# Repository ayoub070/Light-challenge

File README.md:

# Light-challenge
 This is the kicad file of the light challenge Printed Circuit Board

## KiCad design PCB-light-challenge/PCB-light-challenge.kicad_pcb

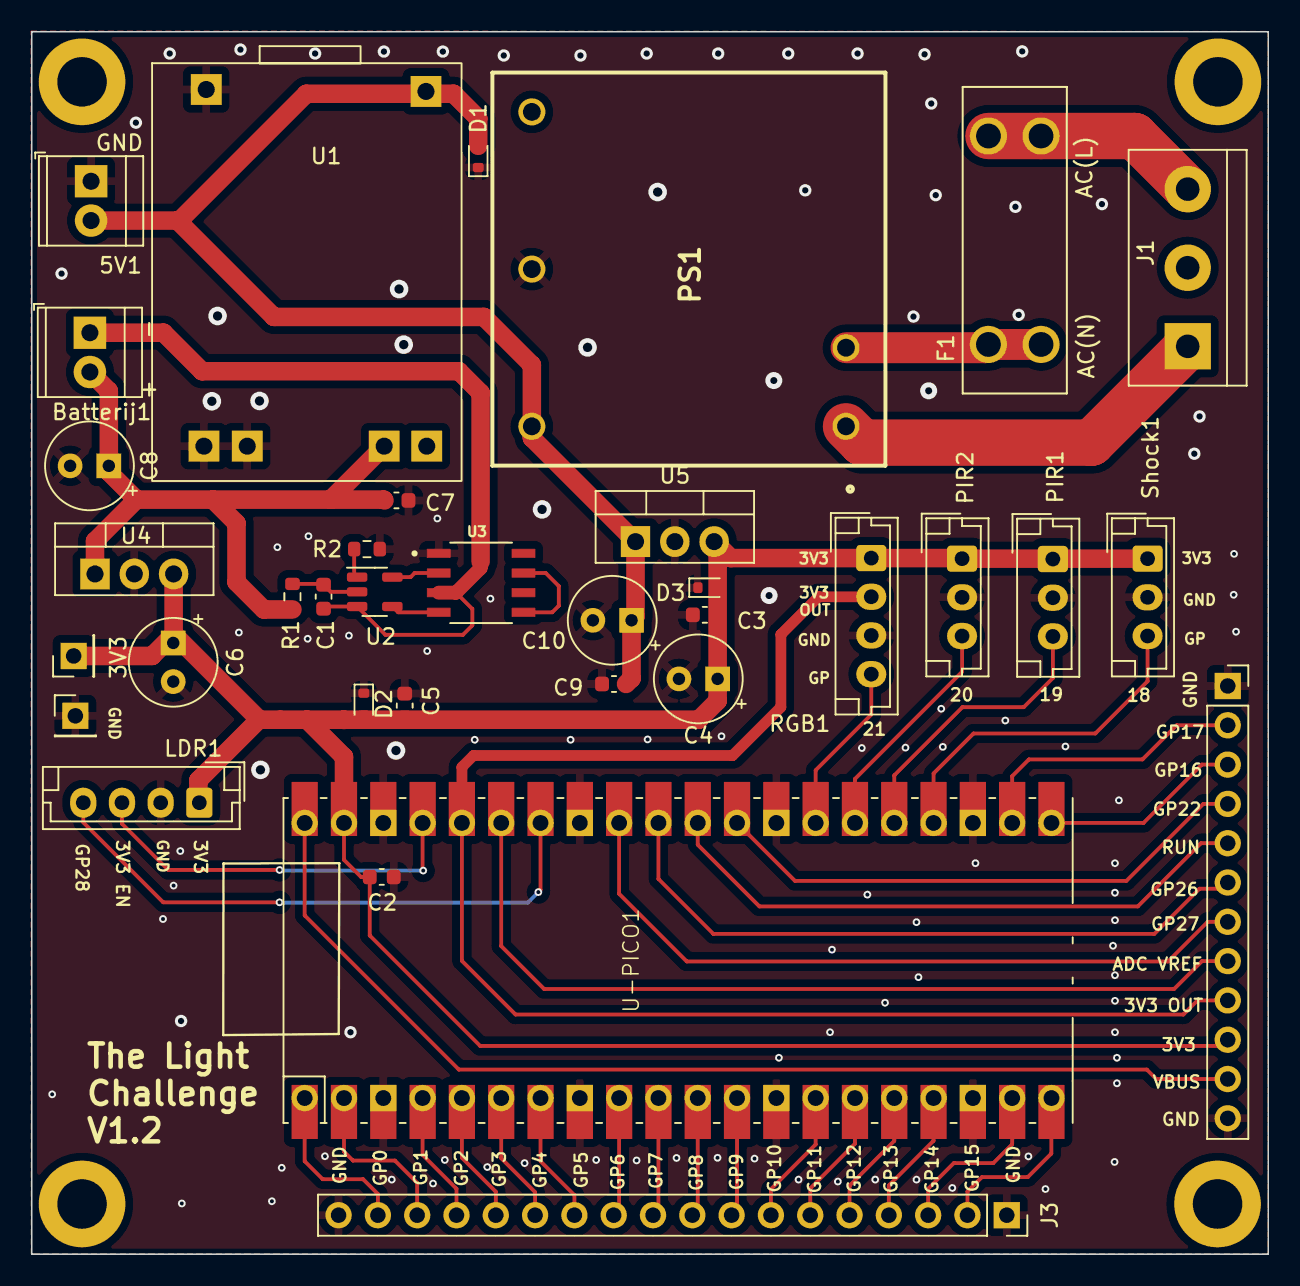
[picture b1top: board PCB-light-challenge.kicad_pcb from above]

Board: 2 copper layers, 79.9 x 79.0 mm, 39 parts (0 on the bottom side), 44 nets.

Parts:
3V3: Conn_01x01_Socket; PinHeader_1x01_P2.54mm_Vertical
5V1: Conn_01x02_Socket; TerminalBlock_TE_282834-2_1x02_P2.54mm_Horizontal
Batterij1: Screw_Terminal_01x02; TerminalBlock_TE_282834-2_1x02_P2.54mm_Horizontal
C1, C2, C3, C5, C7, C9: 100n; C_0603_1608Metric
C4, C6, C8, C10: C_Polarized; CP_Radial_Tantal_D5.5mm_P2.50mm
D1, D2, D3: ESD9B3.3ST5G; D_SOD-523
F1: Fuse; FUSE_3557-2
H1, H2, H3, H4: MountingHole; MountingHole_3.2mm_M3_DIN965_Pad
J1: Screw_Terminal_01x03; TerminalBlock_bornier-3_P5.08mm
J3: Conn_01x18_Socket; PinSocket_1x18_P2.54mm_Vertical
J4: Conn_01x12_Socket; PinSocket_1x12_P2.54mm_Vertical
LDR1: LDR; JST_EH_B4B-EH-A_1x04_P2.50mm_Vertical
P-1: Conn_01x01_Socket; PinHeader_1x01_P2.54mm_Vertical
PIR1, PIR2: JST_EH_B3B-EH-A_1x03_P2.50mm_Vertical
PS1: TMPS_05-105; TMPS05-105
R1: 330; R_0603_1608Metric
R2: 2K7; R_0603_1608Metric
RGB1: RGB; JST_EH_B4B-EH-A_1x04_P2.50mm_Vertical
Shock1: JST_EH_B3B-EH-A_1x03_P2.50mm_Vertical
U1: bms
U2: AP9101CK; SOT-23-5
U3: SP8K32FRATB; SOIC127P600X175-8N
U4, U5: TO-220-3_Vertical
U-PICO1: PICO

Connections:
3V3: 3V3.1, C2.1, C3.1, C4.1, C5.1, C6.1, D2.2 (A2), D3.2 (A2), J4.10, LDR1.1, PIR1.1 (VCC), PIR2.1 (VCC), RGB1.1, Shock1.1 (VCC), U4.3 (OUT), U5.3 (OUT), U-PICO1.39 (VSYS)
3V3 EN: LDR1.3, U-PICO1.37 (3V3_EN)
3V3 OUT: J4.9, RGB1.2, U-PICO1.36 (3V3(OUT))
+5V: 5V1.2, C9.1, C10.1, D1.2 (A2), PS1.5 (+VOUT), U1.6 (IN+), U5.1 (IN)
/Battery_charger/Fuse: F1.1_1, F1.1_2, PS1.2 (AC(L))
/Battery_charger/Fuse_in: F1.2_1, F1.2_2, J1.3
/Battery_charger/GNDAC: J1.1, PS1.1 (AC(N))
ADC VREF: J4.8, U-PICO1.35 (ADC_VREF)
Batterij+: Batterij1.2, C7.1, C8.1, R1.1, U1.4 (BAT+), U4.1 (IN)
Batterij-: Batterij1.1, C1.2, U2.3 (VSS), U3.3
GP0: J3.17, U-PICO1.1 (GP0)
GP1: J3.16, U-PICO1.2 (GP1)
GP2: J3.15, U-PICO1.4 (GP2)
GP3: J3.14, U-PICO1.5 (GP3)
GP4: J3.13, U-PICO1.6 (GP4)
GP5: J3.12, U-PICO1.7 (GP5)
GP6: J3.11, U-PICO1.9 (GP6)
GP7: J3.10, U-PICO1.10 (GP7)
GP8: J3.9, U-PICO1.11 (GP8)
GP9: J3.8, U-PICO1.12 (GP9)
GP10: J3.7, U-PICO1.14 (GP10)
GP11: J3.6, U-PICO1.15 (GP11)
GP12: J3.5, U-PICO1.16 (GP12)
GP13: J3.4, U-PICO1.17 (GP13)
GP14: J3.3, U-PICO1.19 (GP14)
GP15: J3.2, U-PICO1.20 (GP15)
GP16: J4.3, U-PICO1.21 (GP16)
GP17: J4.2, U-PICO1.22 (GP17)
GP18: Shock1.3 (Digital_Out), U-PICO1.24 (GP18)
GP19: PIR1.3 (OUT_data), U-PICO1.25 (GP19)
GP20: PIR2.3 (OUT_data), U-PICO1.26 (GP20)
GP21: RGB1.4, U-PICO1.27 (GP21)
GP22: J4.4, U-PICO1.29 (GP22)
GP26: J4.6, U-PICO1.31 (GP26-ADC0)
GP27: J4.7, U-PICO1.32 (GP27-ADC1)
GP28: LDR1.4, U-PICO1.34 (GP28-ADC2)
unnamed: U2.5 (CO), U3.2
unnamed: U2.4 (DO), U3.4
unnamed: C1.1, R1.2, U2.2 (VDD)
unnamed: R2.2, U2.1 (VM)
unnamed: U3.5, U3.7
P-: 5V1.1, C2.2, C3.2, C4.2, C5.2, C6.2, C7.2, C8.2, C9.2, C10.2, D1.1 (A1), D2.1 (A1), D3.1 (A1), J3.1, J3.18, J4.1, J4.12, LDR1.2, P-1.1, PIR1.2 (GND), PIR2.2 (GND), PS1.4 (-VOUT), R2.1, RGB1.3, Shock1.2 (GND), U1.1 (OUT-), U1.3 (BAT-), U1.5 (IN-), U3.1, U4.2 (GND), U5.2 (GND), U-PICO1.3 (GND), U-PICO1.8 (GND), U-PICO1.13 (GND), U-PICO1.18 (GND), U-PICO1.23 (GND), U-PICO1.28 (GND), U-PICO1.33 (GND-AGND), U-PICO1.38 (GND)
RUN: J4.5, U-PICO1.30 (RUN)
VBUS: J4.11, U-PICO1.40 (VBUS)

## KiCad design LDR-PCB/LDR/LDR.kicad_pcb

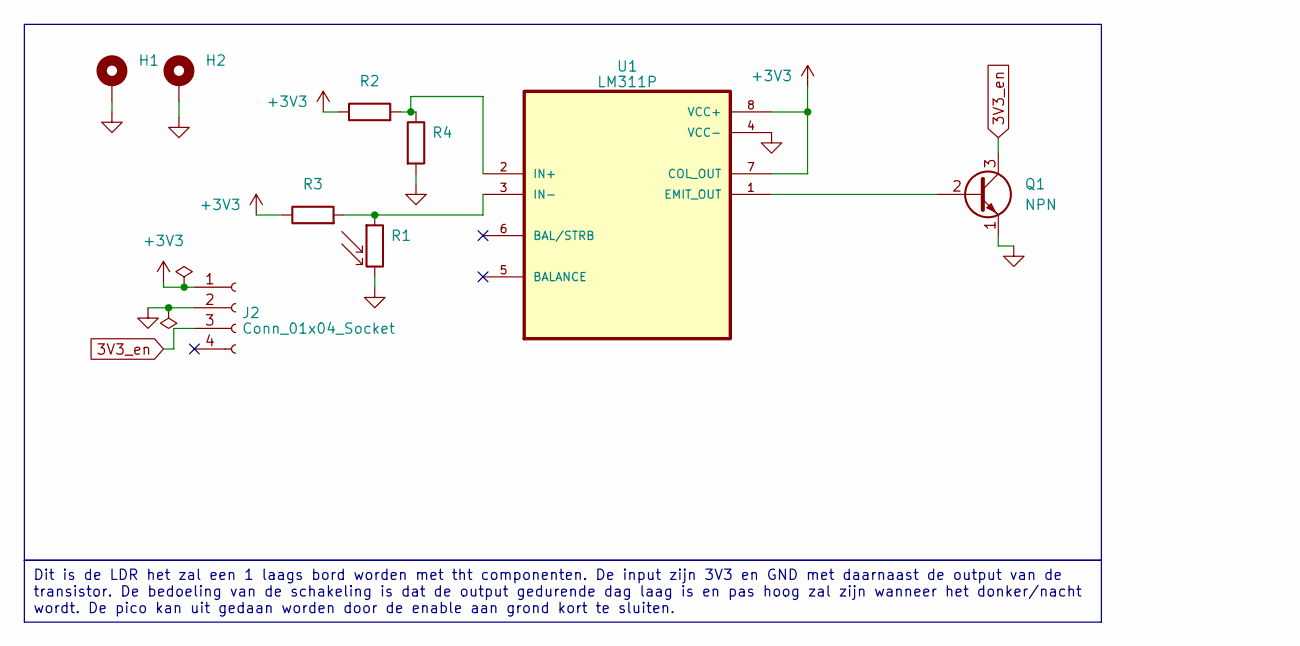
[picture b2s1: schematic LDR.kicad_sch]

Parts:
H1, H2: MountingHole_Pad; MountingHole_2.2mm_M2_ISO14580_Pad
J2: Conn_01x04_Socket; JST_EH_B4B-EH-A_1x04_P2.50mm_Vertical
Q1: NPN; TO-92_Inline
R1: R_Photo; R_Axial_DIN0204_L3.6mm_D1.6mm_P5.08mm_Horizontal
R2, R3: 2K2; R_Axial_DIN0204_L3.6mm_D1.6mm_P5.08mm_Horizontal
R4: 1K8; R_Axial_DIN0204_L3.6mm_D1.6mm_P5.08mm_Horizontal
U1: LM311P; DIP794W45P254L959H508Q8

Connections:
3V3_en: J2.3, Q1.3 (C)
+3V3: J2.1, R2.1, R3.1, U1.7 (COL_OUT), U1.8 (VCC+)
GND: H1.1, H2.1, J2.2, Q1.1 (E), R1.2, R4.2, U1.4 (VCC-)
unnamed: Q1.2 (B), U1.1 (EMIT_OUT)
unnamed: R2.2, R4.1, U1.2 (IN+)
unnamed: R1.1, R3.2, U1.3 (IN-)

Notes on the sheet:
Dit is de LDR het zal een 1 laags bord worden met tht componenten. De input zijn 3V3 en GND met daarnaast de output van de transistor. De bedoeling van de schakeling is dat de output gedurende dag laag is en pas hoog zal zijn wanneer het donker/nacht wordt. De pico kan uit gedaan worden door de ena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

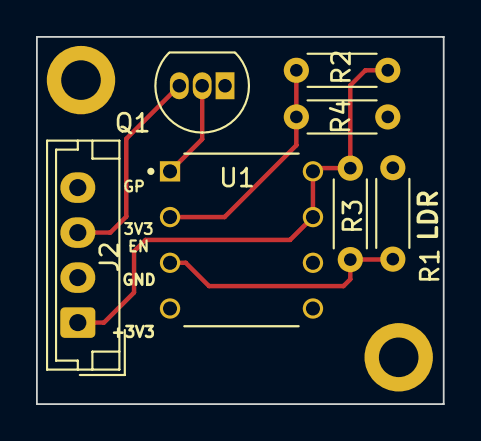
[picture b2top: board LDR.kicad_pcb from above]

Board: 2 copper layers, 22.6 x 20.4 mm, 9 parts (0 on the bottom side), 6 nets.

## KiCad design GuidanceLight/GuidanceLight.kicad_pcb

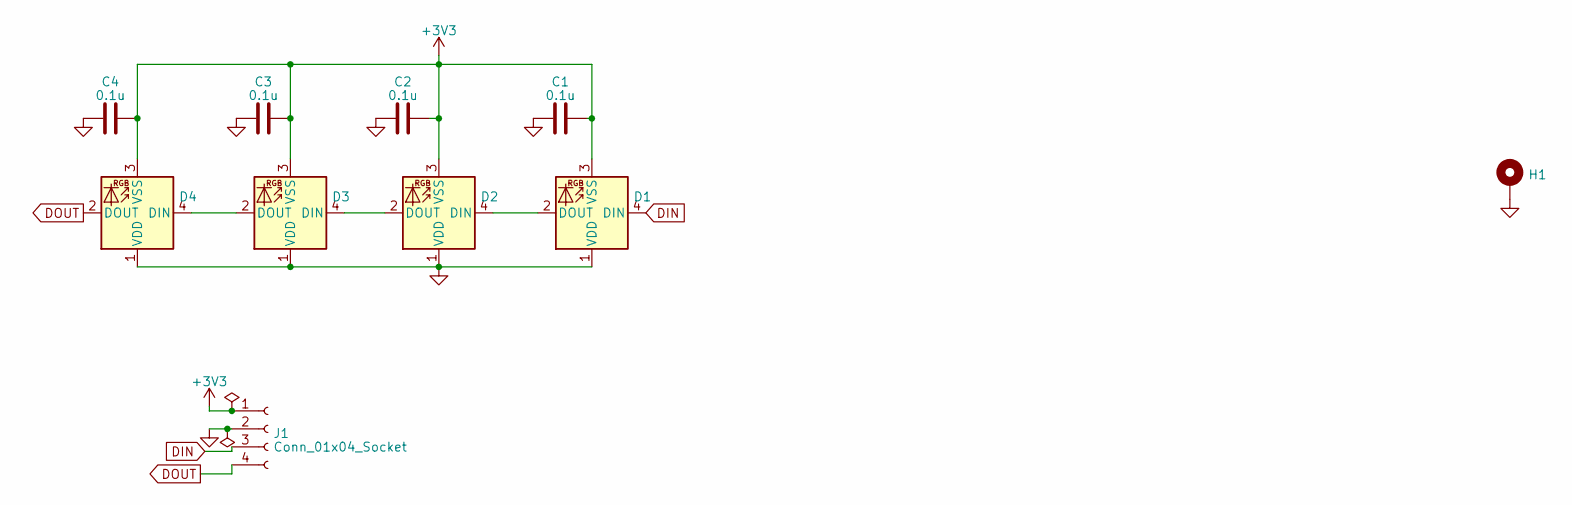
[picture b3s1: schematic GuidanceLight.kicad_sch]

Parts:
C1, C2, C3, C4: 0.1u; C_0603_1608Metric
D1, D2, D3, D4: WS2812B; LED_WS2812B_PLCC4_5.0x5.0mm_P3.2mm
H1: MountingHole_Pad; MountingHole_2.2mm_M2_DIN965_Pad
J1: Conn_01x04_Socket; PinHeader_1x04_P2.54mm_Horizontal

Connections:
+3V3: C1.2, C2.2, C3.2, C4.2, D1.3 (VSS), D2.3 (VSS), D3.3 (VSS), D4.3 (VSS), J1.1
DIN: D1.4 (DIN), J1.3
DOUT: D4.2 (DOUT), J1.4
GND: C1.1, C2.1, C3.1, C4.1, D1.1 (VDD), D2.1 (VDD), D3.1 (VDD), D4.1 (VDD), H1.1, J1.2
unnamed: D1.2 (DOUT), D2.4 (DIN)
unnamed: D2.2 (DOUT), D3.4 (DIN)
unnamed: D3.2 (DOUT), D4.4 (DIN)

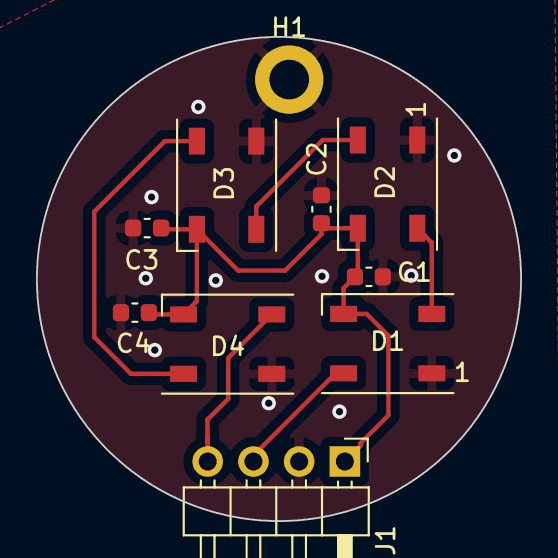
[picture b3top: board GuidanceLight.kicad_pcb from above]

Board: 2 copper layers, 26.9 x 26.9 mm, 10 parts (0 on the bottom side), 7 nets.

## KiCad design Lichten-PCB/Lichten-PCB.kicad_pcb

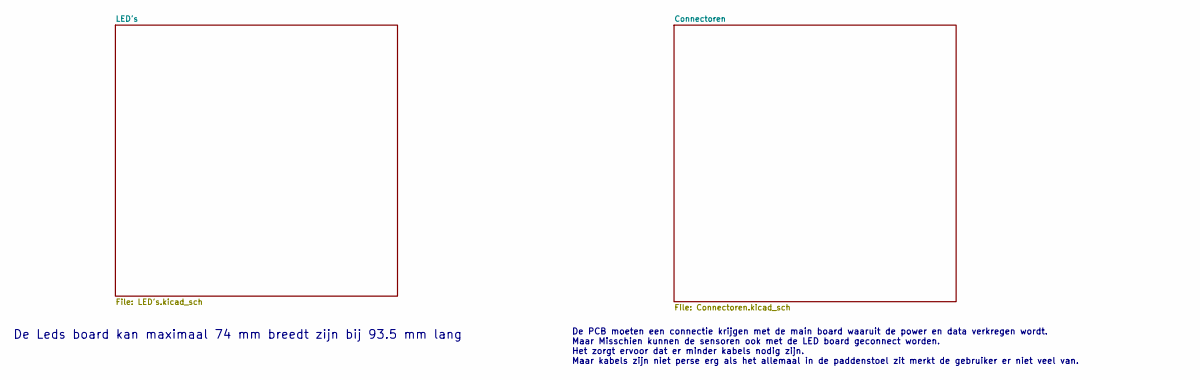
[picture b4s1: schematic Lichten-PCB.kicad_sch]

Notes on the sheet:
De Leds board kan maximaal 74 mm breedt zijn bij 93.5 mm lang
De PCB moeten een connectie krijgen met de main board waaruit de power en data verkregen wordt. Maar Misschien kunnen de sensoren ook met de LED board geconnect worden. Het zorgt ervoor dat er minder kabels nodig zijn. Maar kabels zijn niet perse erg als het allemaal in de paddenstoel zit merkt de 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

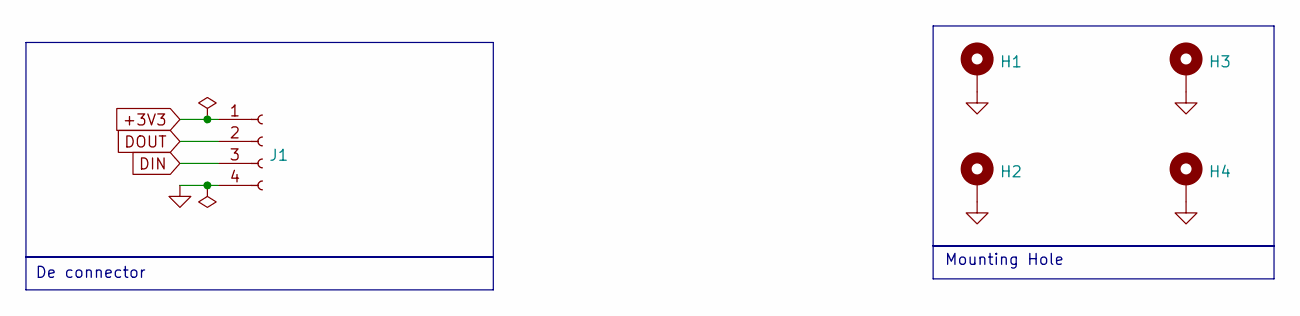
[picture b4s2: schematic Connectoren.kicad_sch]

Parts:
H1, H2, H3, H4: MountingHole_Pad; MountingHole_2.2mm_M2_DIN965_Pad
J1: Conn_01x04_Socket; TerminalBlock_4Ucon_1x04_P3.50mm_Horizontal

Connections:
+3V3: J1.1; also elsewhere on the board
DIN: J1.3; also elsewhere on the board
DOUT: J1.2; also elsewhere on the board
GND: H1.1, H2.1, H3.1, H4.1, J1.4; also elsewhere on the board

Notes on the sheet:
De connector
Mounting Hole

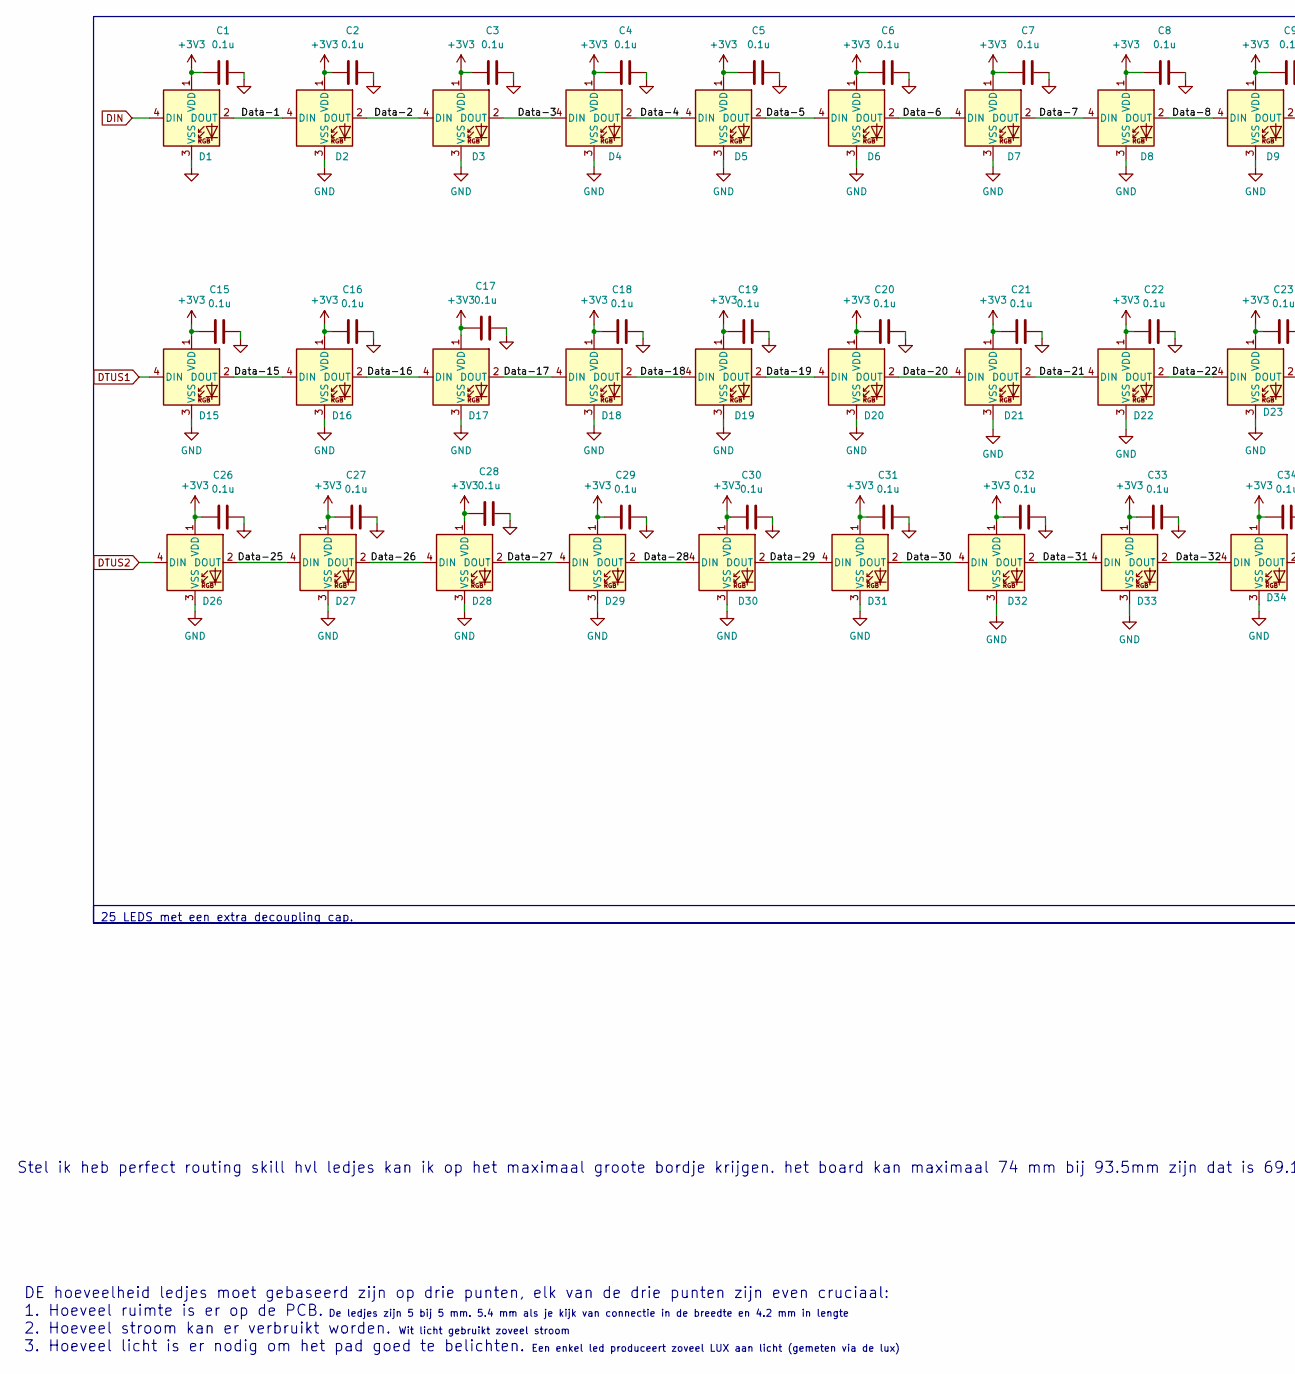
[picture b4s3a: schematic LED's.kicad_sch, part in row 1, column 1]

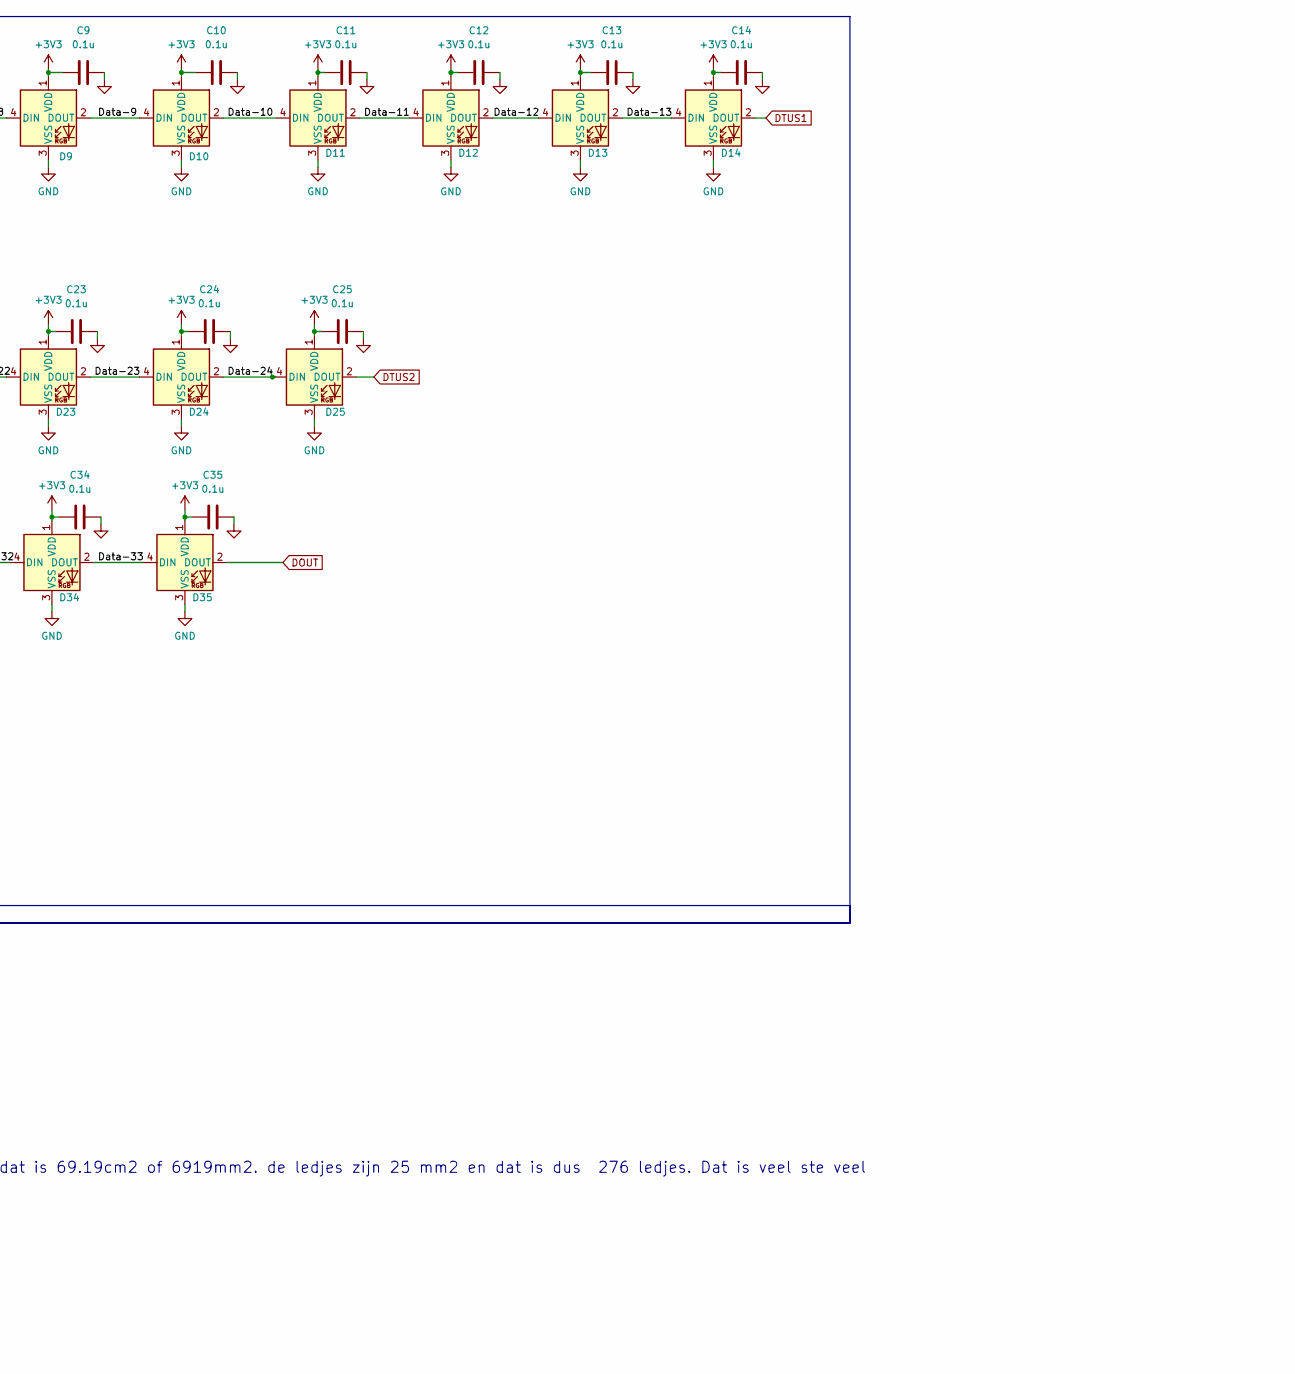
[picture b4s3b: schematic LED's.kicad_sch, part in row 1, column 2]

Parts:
C1, C2, C3, C4, C5, C6, C7, C8, C9, C10, C11, C12, C13, C14, C15, C16, C17, C18, C19, C20, C21, C22, C23, C24, C25, C26, C27, C28, C29, C30, C31, C32, C33, C34, C35: 0.1u; C_0603_1608Metric
D1, D2, D3, D4, D5, D6, D7, D8, D9, D10, D11, D12, D13, D14, D15, D16, D17, D18, D19, D20, D21, D22, D23, D24, D25, D26, D27, D28, D29, D30, D31, D32, D33, D34, D35: WS2812B; LED_WS2812B_PLCC4_5.0x5.0mm_P3.2mm

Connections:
+3V3: C1.1, C2.1, C3.1, C4.1, C5.1, C6.1, C7.1, C8.1, C9.1, C10.1, C11.1, C12.1, C13.1, C14.1, C15.1, C16.1, C17.1, C18.1, C19.1, C20.1, C21.1, C22.1, C23.1, C24.1, C25.1, C26.1, C27.1, C28.1, C29.1, C30.1, C31.1, C32.1, C33.1, C34.1, C35.1, D1.1 (VDD), D2.1 (VDD), D3.1 (VDD), D4.1 (VDD), D5.1 (VDD), D6.1 (VDD), D7.1 (VDD), D8.1 (VDD), D9.1 (VDD), D10.1 (VDD), D11.1 (VDD), D12.1 (VDD), D13.1 (VDD), D14.1 (VDD), D15.1 (VDD), D16.1 (VDD), D17.1 (VDD), D18.1 (VDD), D19.1 (VDD), D20.1 (VDD), D21.1 (VDD), D22.1 (VDD), D23.1 (VDD), D24.1 (VDD), D25.1 (VDD), D26.1 (VDD), D27.1 (VDD), D28.1 (VDD), D29.1 (VDD), D30.1 (VDD), D31.1 (VDD), D32.1 (VDD), D33.1 (VDD), D34.1 (VDD), D35.1 (VDD); also elsewhere on the board
/LED's/Data-1: D1.2 (DOUT), D2.4 (DIN)
/LED's/Data-2: D2.2 (DOUT), D3.4 (DIN)
/LED's/Data-3: D3.2 (DOUT), D4.4 (DIN)
/LED's/Data-4: D4.2 (DOUT), D5.4 (DIN)
/LED's/Data-5: D5.2 (DOUT), D6.4 (DIN)
/LED's/Data-6: D6.2 (DOUT), D7.4 (DIN)
/LED's/Data-7: D7.2 (DOUT), D8.4 (DIN)
/LED's/Data-8: D8.2 (DOUT), D9.4 (DIN)
/LED's/Data-9: D9.2 (DOUT), D10.4 (DIN)
/LED's/Data-10: D10.2 (DOUT), D11.4 (DIN)
/LED's/Data-11: D11.2 (DOUT), D12.4 (DIN)
/LED's/Data-12: D12.2 (DOUT), D13.4 (DIN)
/LED's/Data-13: D13.2 (DOUT), D14.4 (DIN)
/LED's/Data-15: D15.2 (DOUT), D16.4 (DIN)
/LED's/Data-16: D16.2 (DOUT), D17.4 (DIN)
/LED's/Data-17: D17.2 (DOUT), D18.4 (DIN)
/LED's/Data-18: D18.2 (DOUT), D19.4 (DIN)
/LED's/Data-19: D19.2 (DOUT), D20.4 (DIN)
/LED's/Data-20: D20.2 (DOUT), D21.4 (DIN)
/LED's/Data-21: D21.2 (DOUT), D22.4 (DIN)
/LED's/Data-22: D22.2 (DOUT), D23.4 (DIN)
/LED's/Data-23: D23.2 (DOUT), D24.4 (DIN)
/LED's/Data-24: D24.2 (DOUT), D25.4 (DIN)
/LED's/Data-25: D26.2 (DOUT), D27.4 (DIN)
/LED's/Data-26: D27.2 (DOUT), D28.4 (DIN)
/LED's/Data-27: D28.2 (DOUT), D29.4 (DIN)
/LED's/Data-28: D29.2 (DOUT), D30.4 (DIN)
/LED's/Data-29: D30.2 (DOUT), D31.4 (DIN)
/LED's/Data-30: D31.2 (DOUT), D32.4 (DIN)
/LED's/Data-31: D32.2 (DOUT), D33.4 (DIN)
/LED's/Data-32: D33.2 (DOUT), D34.4 (DIN)
/LED's/Data-33: D34.2 (DOUT), D35.4 (DIN)
DIN: D1.4 (DIN); also elsewhere on the board
DOUT: D35.2 (DOUT); also elsewhere on the board
DTUS1: D14.2 (DOUT), D15.4 (DIN)
DTUS2: D25.2 (DOUT), D26.4 (DIN)
GND: C1.2, C2.2, C3.2, C4.2, C5.2, C6.2, C7.2, C8.2, C9.2, C10.2, C11.2, C12.2, C13.2, C14.2, C15.2, C16.2, C17.2, C18.2, C19.2, C20.2, C21.2, C22.2, C23.2, C24.2, C25.2, C26.2, C27.2, C28.2, C29.2, C30.2, C31.2, C32.2, C33.2, C34.2, C35.2, D1.3 (VSS), D2.3 (VSS), D3.3 (VSS), D4.3 (VSS), D5.3 (VSS), D6.3 (VSS), D7.3 (VSS), D8.3 (VSS), D9.3 (VSS), D10.3 (VSS), D11.3 (VSS), D12.3 (VSS), D13.3 (VSS), D14.3 (VSS), D15.3 (VSS), D16.3 (VSS), D17.3 (VSS), D18.3 (VSS), D19.3 (VSS), D20.3 (VSS), D21.3 (VSS), D22.3 (VSS), D23.3 (VSS), D24.3 (VSS), D25.3 (VSS), D26.3 (VSS), D27.3 (VSS), D28.3 (VSS), D29.3 (VSS), D30.3 (VSS), D31.3 (VSS), D32.3 (VSS), D33.3 (VSS), D34.3 (VSS), D35.3 (VSS); also elsewhere on the board

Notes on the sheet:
25 LEDS met een extra decoupling cap.
DE hoeveelheid ledjes moet gebaseerd zijn op drie punten, elk van de drie punten zijn even cruciaal: 1. Hoeveel ruimte is er op de PCB. 2. Hoeveel stroom kan er verbruikt worden. 3. Hoeveel licht is er nodig om het pad goed te belichten.
Stel ik heb perfect routing skill hvl ledjes kan ik op het maximaal groote bordje krijgen. het board kan maximaal 74 mm bij 93.5mm zijn dat is 69.19cm2 of 6919mm2. de ledjes zijn 25 mm2 en dat is dus 276 ledjes. Dat is veel ste veel
Wit licht gebruikt zoveel stroom
Een enkel led produceert zoveel LUX aan licht (gemeten via de lux)
De ledjes zijn 5 bij 5 mm. 5.4 mm als je kijk van connectie in de breedte en 4.2 mm in lengte

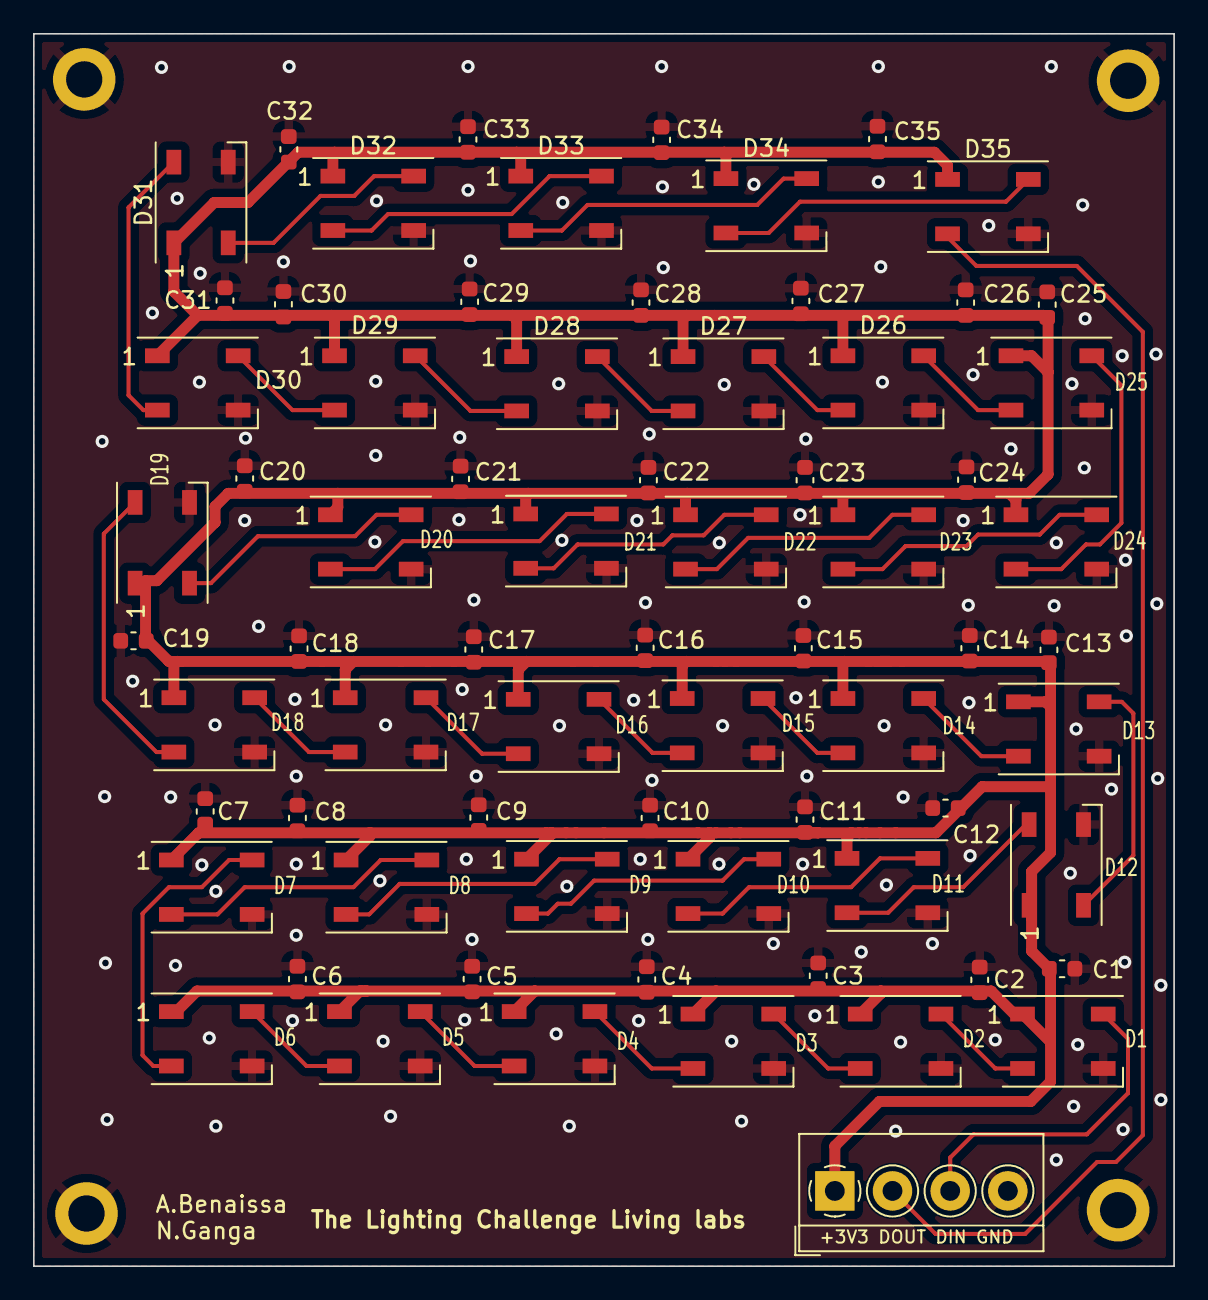
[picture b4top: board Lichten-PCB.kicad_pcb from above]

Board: 2 copper layers, 69.2 x 74.8 mm, 75 parts (0 on the bottom side), 38 nets.

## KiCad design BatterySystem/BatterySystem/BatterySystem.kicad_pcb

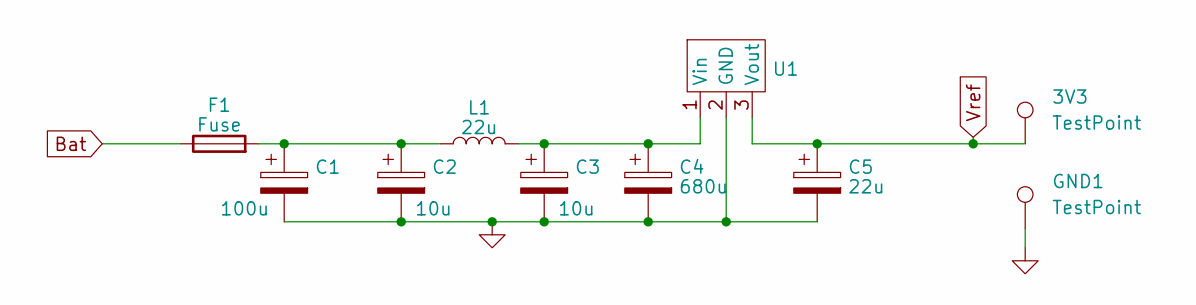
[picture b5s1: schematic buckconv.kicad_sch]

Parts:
3V3: TestPoint; TestPoint_Keystone_5005-5009_Compact
C1: 100u; CP_Radial_D8.0mm_P3.50mm
C2, C3: 10u; C_1206_3216Metric
C4: 680u; CP_Radial_D12.5mm_P5.00mm
C5: 22u; C_0805_2012Metric
F1: Fuse; Fuseholder_Clip-5x20mm_Eaton_1A5601-01_Inline_P20.80x6.76mm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
GND1: TestPoint; TestPoint_Keystone_5005-5009_Compact
L1: 22u; L_Bourns_SRP1038C_10.0x10.0mm
U1: 3.3V; VR20S3V3

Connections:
Bat: F1.1; also elsewhere on the board
GND: C1.2, C2.2, C3.2, C4.2, C5.2, GND1.1, U1.2 (GND); also elsewhere on the board
unnamed: C1.1, C2.1, F1.2, L1.1
unnamed: C3.1, C4.1, L1.2, U1.1 (Vin)
Vref: 3V3.1, C5.1, U1.3 (Vout); also elsewhere on the board

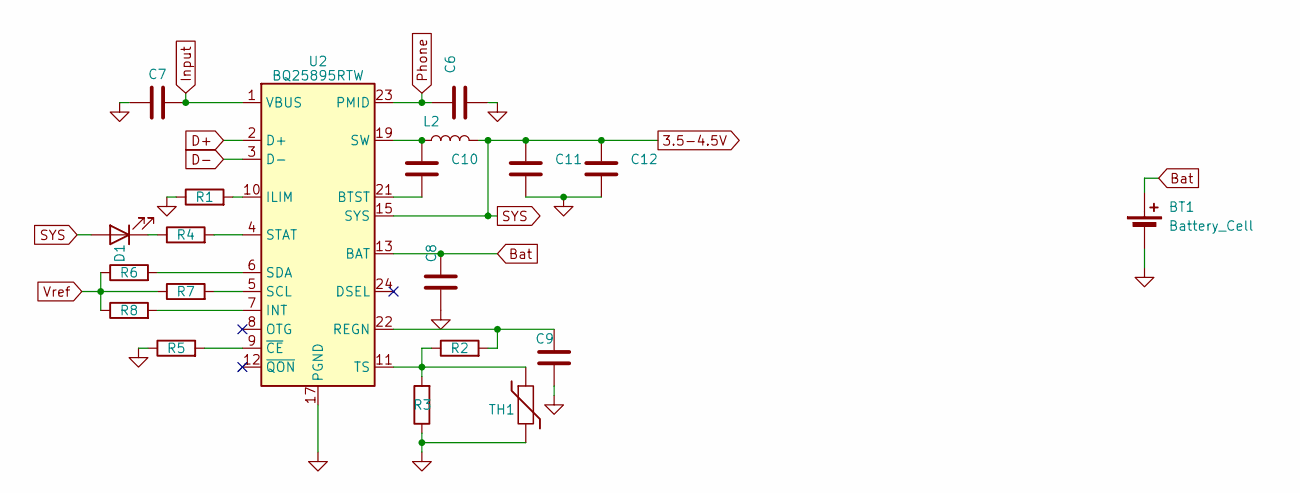
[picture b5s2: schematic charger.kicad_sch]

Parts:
BT1: Battery_Cell; BatteryHolder_Keystone_1042_1x18650
C6: 8.2u; C_1206_3216Metric
C7: 1u; R_0603_1608Metric
C8, C11, C12: 10u; C_0603_1608Metric
C9: 4.7u; C_0603_1608Metric
C10: 47n; C_0603_1608Metric
D1: LED; LED_0603_1608Metric
L2: 2.2u
R1: 260; R_0603_1608Metric
R2: 5.23k; R_0603_1608Metric
R3: 30.1k; R_0603_1608Metric
R4: 2.2k; R_0603_1608Metric
R5: 4.7k; R_0603_1608Metric
R6, R7, R8: 10k; R_0603_1608Metric
TH1: 10k; R_0603_1608Metric
U2: BQ25895RTW; Texas_S-PWQFN-N24_EP2.7x2.7mm_ThermalVias

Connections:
3.5-4.5V: C11.2, C12.2, D1.2 (A), L2.2, U2.15 (SYS), U2.16 (SYS); also elsewhere on the board
Bat: BT1.1 (+), C8.2, U2.13 (BAT), U2.14 (BAT); also elsewhere on the board
D+: U2.2 (D+); also elsewhere on the board
D-: U2.3 (D-); also elsewhere on the board
GND: BT1.2 (-), C6.2, C7.2, C8.1, C9.1, C11.1, C12.1, R1.1, R3.1, R5.1, TH1.2, U2.17 (PGND), U2.18 (PGND), U2.25 (PGND); also elsewhere on the board
Input: C7.1, U2.1 (VBUS); also elsewhere on the board
unnamed: C10.2, L2.1, U2.19 (SW), U2.20 (SW)
unnamed: D1.1 (K), R4.1
unnamed: C10.1, U2.21 (BTST)
unnamed: R1.2, U2.10 (ILIM)
unnamed: R8.2, U2.7 (INT)
unnamed: C9.2, R2.2, U2.22 (REGN)
unnamed: R7.2, U2.5 (SCL)
unnamed: R6.2, U2.6 (SDA)
unnamed: R4.2, U2.4 (STAT)
unnamed: R2.1, R3.2, TH1.1, U2.11 (TS)
unnamed: R5.2, U2.9 (~CE)
Phone: C6.1, U2.23 (PMID)
Vref: R6.1, R7.1, R8.1; also elsewhere on the board

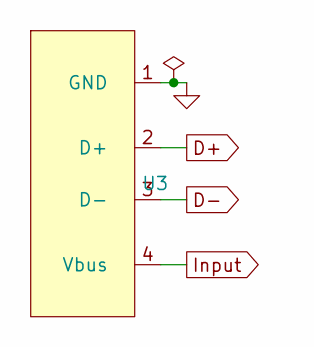
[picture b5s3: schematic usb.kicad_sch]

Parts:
U3: USB-C 2.0 Female to DIP Adapter

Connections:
D+: U3.2 (D+); also elsewhere on the board
D-: U3.3 (D-); also elsewhere on the board
GND: U3.1 (GND); also elsewhere on the board
Input: U3.4 (Vbus); also elsewhere on the board

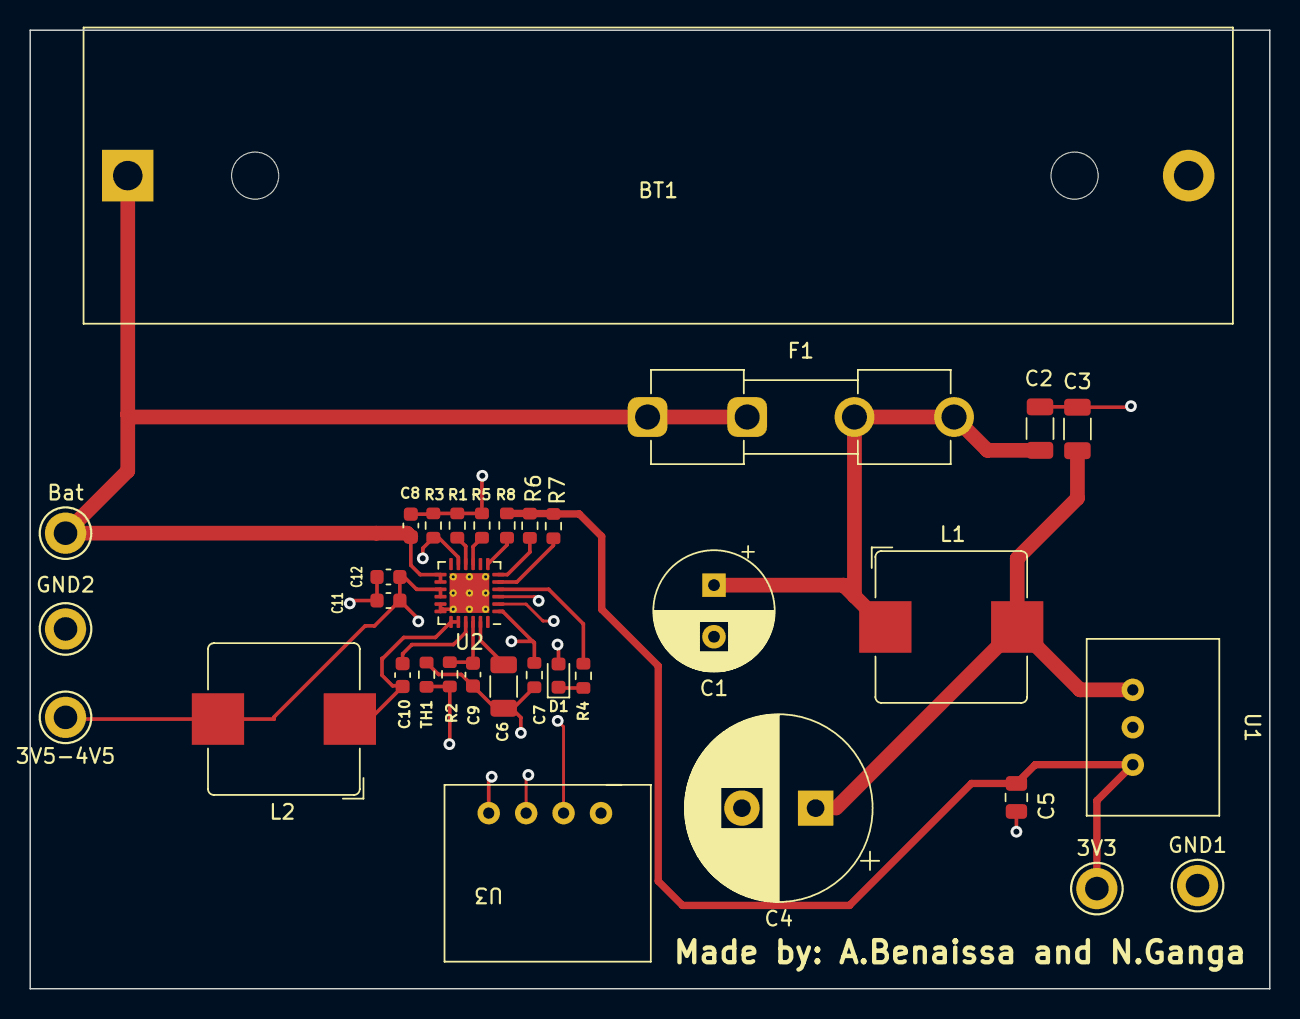
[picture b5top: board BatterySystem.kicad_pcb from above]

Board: 4 copper layers, 84.1 x 65.0 mm, 34 parts (0 on the bottom side), 21 nets.

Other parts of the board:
3V5-4V5: TestPoint; TestPoint_Keystone_5005-5009_Compact
Bat: TestPoint; TestPoint_Keystone_5005-5009_Compact
GND2: TestPoint; TestPoint_Keystone_5005-5009_Compact

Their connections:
3.5-4.5V: 3V5-4V5.1; also elsewhere on the board
Bat: Bat.1; also elsewhere on the board
GND: GND2.1; also elsewhere on the board

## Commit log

2023-08-30 Kicad file aangemaakt
2023-09-01 Rasberry_pico symbol gemaakt in de light challenge map
2023-09-01 PICO toegevoegd in schema
2023-09-01 Library delen
2023-09-01 Library toegevoegd
2023-09-01 Opnieuw
2023-09-01 pico footprint
2023-09-06 Hierarchische blad toegevoegd voor de microcontroller en battery charger
    Dit moet gedaan worden voor elke deel van het totale circuit. Dit maakt de file beter leesbaar
2023-09-06 Beetje meer bladen toegevoegd
2023-09-07 USB blad weg gehaald plus BQ25895 toegevoegd
2023-09-08 Battery test PCB gemaakt met hirarchical BMS en charger sheets
2023-09-08 DCDC Converter symbol & footprint
2023-09-08 Circuit of the DCDC conv
2023-09-08 BQ25895 toegevoegd in test pcb
2023-09-11 Charger circuit gemaakt
2023-09-11 USB toegevoegd
2023-09-12 Footprints toegevoegd aan battery charger
2023-09-12 footprint buckconv
2023-09-12 Batterij en houder toegevoegd
2023-09-12 footprint buckconv weer toegevoegd
2023-09-12 Componenten footprint toegevoegd
    usb c footprint is met niks aangesloten. raar
2023-09-12 USB connectie
2023-09-12 Beetje gewerkt aan routen van de PCB en positioneren van componenten
2023-09-12 Traces toegevoegd
2023-09-13 Buck converter gedaan en meer test point toegevoegd
2023-09-13 PCB tracing afgemaakt
2023-09-13 Tracing afgemaakt
2023-09-15 new mapje voor code gemaakt
    Heb de libraries van PWM en voor de ledje alvast gedownload.
2023-09-15 Code om 1 lampje rood te maken
2023-09-15 code gekoppieerd
2023-09-18 LEDs individueel aangestuurd oom stroom te meten
2023-09-19 Code coor PIR
2023-09-19 Test code voor PIR
2023-09-19 Made the code work
2023-09-19 Code met RGB
2023-09-19 Lichje aangezet
2023-09-20 Update main.cpp
    working code with one PIR
2023-09-20 Update main.cpp
    Alle lichten aangestuurd met PIR
2023-09-25 Update main.cpp
    Code
2023-09-25 Update main.cpp
    Code is bijna Af en het werkt . met beide PIR sensors en shok sensors
2023-09-25 Update main.cpp
    comments toegevoegd aan de code
2023-09-28 Update main.cpp
    stroommeting gedaan met de code
2023-09-28 Lampie PCB begin
2023-09-28 Capacitor waardes toegevoegd en coonectoren toegevoegd
2023-10-02 Footprints toegevoegd
2023-10-02 Componenten geplaatst
    Paar fouten opgelost namen juist gemaakt en niet gelinked connecties vastgemaakt.
2023-10-02 Bekabeling van de power en data
2023-10-02 alle 3V3 geconnect
2023-10-02 ground plane toegevoegd
2023-10-02 Via geplaatst en beetje verbeterd
2023-10-02 Edge cuts en via toegevoegd met wat silk screen
    Misschien op de achterkant een leuke foto van een aap
2023-10-02 Foto toegevoegd
2023-10-03 Trace dikte en mounting hole toegevoegd
2023-10-04 Nieuwe Via aan de onderkant toegevoegd pinout back silkscreen aangemaakt en correct gespiegeld. en god said there was light goed gequote dit keer.
2023-10-04 Oke nu is de quote goed (hopelijjk)
2023-10-05 PCB vergroot
2023-10-06 Via's geplaatst en aap verwisseld met panda
    panda's zijn in real live al zwart wit dus voor silk screen is easy.
2023-10-06 Trace dikte aangepast naar 0.667 mm
2023-10-06 Footprint van connector aangepast
2023-10-06 3D van connector toegevoegd
2023-10-09 Via's geplaatst en DOUT gereroute
2023-10-09 Guidance Light PCB toegevoegd
2023-10-10 Nieuwe gerber file aangemaakt en drill holes toegevoegd dit is ook in de zip geupdate
2023-10-24 Library symbol met footprint toegevoegd van PIR sensor
2023-10-24 symbool gezocht op mijn laptop
2023-10-25 Batterij charger foorprint en symbol toegevoegd, BMS schema getekend , LDO symbol en footprint toegevoegd
2023-10-25 schock sensor toegevoegd footprit plus symbol
2023-11-02 one layer LDR board begin
2023-11-02 RP2040 pinout toegevoegd met naam
2023-11-03 LDR circuit is done nu nog plaatsen
2023-11-03 Footprint toegevoegd
2023-11-03 opamp footprint toegevoegd
2023-11-06 Footprints toegevoegd van alles
2023-11-06 Traco footprint toegevoegd
2023-11-06 LDR zal nu de 3v3_en omlaag trekken om de pico uit te zetten
    Gedeeltelijke merge
2023-11-07 Mainboard onderdelen gesorteerd
2023-11-07 PCB LDR af (bijna)
2023-11-07 merge
2023-11-08 main board aangepast en ground toegevoegd
2023-11-08 EDS protection en fuse toegevoegd
    we moeten nog wel footprints checken
2023-11-09 PCB 80% af
2023-11-10 Kleine aanpassingen gemaakt in het plaatsen van componenten ,traces en tekst
2023-11-10 Footprint van de eds protection device aangepast naar sod 523
    https://nl.farnell.com/en-NL/rohm/rsb6-8smt2n/esd-protection-diode-sod-523-2/dp/2914120
2023-11-13 EDS device bij 230 verwijdert
2023-11-13 PCB is AF en errors fixed
2023-11-14 eds terug gezet
2023-11-14 LDR board is af
2023-11-14 gerber files gemaakt en vias geplaatst in de main pcb
2023-11-14 LDR geber files gemaakt
2023-11-30 Had code gekoppieerd voor een ander test en heb BOM file gemaakt voor het solderen
2023-11-30 BOM file gemaakt voor het solderen
2023-11-30 code van RGB control met potmeter toegevoegd. Ook code voor het testen van een LED toegevoegd
2023-12-05 TP footprint verandert, apparte grond (P-) gemaakt. AC clearance verandert. connector voor PIR verandert
2023-12-05 saved files
2023-12-09 Vias kleiner gemaakt en grond GND genoemd op silkscreen
2023-12-11 Extra caps toegevoegd
2023-12-11 Extra caps
2023-12-17 3V3 OUT voor RGB toegevoegd en footprint van connectoren verandert naar JST
2023-12-18 LDR schakeling update naar LM311P
2023-12-19 LDR connector, silkscreen AC, Mounting hole main pcb aangepast
2023-12-19 AC (L) en (N) weer nagekeken en aangepast
2023-12-20 Footprint charger aangepast, connectoren verder van elkaar geplaatst.
2023-12-21 Via toegevoegd bij AC-fuse
2023-12-21 Gerber gemaakt van main board & LDR
2023-12-23 PCB aangepast naar specificaties van JLCpcb en bestellen
2024-01-08 Com-system
    added code for the mushroom communication system
2024-01-08 lora
2024-01-09 uart
